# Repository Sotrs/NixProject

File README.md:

# NixProject By Sotiris Zannetos Readme Work In Progress
Nixe Clock Project Including Electronics, Software and 3d Designing for Enclosure

By looking at the Nixie Datasheet we know that each tube requires 10 different Inputs to turn each digit on (Will not be using the commas). For this clock I will be using the classic IN-14 Tube.

My MCU of choice is the ATmega328P which is a very popular choice that is also used in Arduino devices, it has a very well established documentation and support and can also be programmed using the Arduino IDE. This is exactly what I need as the Arduino IDE by itself is simple and easy to use and is also very well documented and supported by its community.

Now in order to turn on the tubes we need a driver that can take the digital output of the ATmega and turn on the particular digit we want to light up. We have a few problems we must solve in order to achieve that:
1. The clock we want to create will be a Six-Digit clock "HH:MM:SS" meaning we need 60 individual outputs. Unfortunately the Atmega328P can maxes out at '18', including the analog outputs as digital I/O's.
2. The tubes require a whopping 170V DC in order to light up and about 145V DC to keep running. That is not something we can control using only the digital outputs of a 5V DC Microcontroller.

To solve the first problem we can simply use dedicated Drivers, in fact a BCD-TO-DECIMAL Decoder was made specifically for driving Nixie Tubes known as the **SN74141** or its Soviet Sibling the **K155ID1**. This automatically solves the second problem as well as these drivers were created to handle the high voltage. The use of such drivers makes our project very simple as we can use 1 driver for each tube which brings us down from 60 individual outputs to 24 with each driver requiring 4 bits of info to control the 10 digits.

However, the problem is yet to be solved as 24 outputs are still more than what our MCU can give, we can tackle this problem using an I/O Expander with a Serial Interface. Utilizing THE I^2C Interface of the ATmega we can use I/O Expanders such as the **MCP23017** that will give us 16 extra I/O which are now more than enough of what we need. With that we can sucessfuly drive our nixie tubes using the MCU's Outputs!

We are still missing two critical components in our clock, while the ATmega328P can use its Internal 8MHz crystal Oscillator or an external 16MHz one they are still not very good at time keeping as this is not their intended use, also it will be unable to keep time while it is not powered. This is why we will use an RTC which is a device made for timekeeping. My choice of RTC is the **DS3231** with a simple I2C connection and a cr2032 battery it can keep time with an insane 2PPM accuracy.

Last but definetely not least we will need a DC-DC boost converter, the clock will be powered by 5V DC so we will need to take that 5V and convert it to 170V DC for our tubes. An easy solution to this is to use a premade module made by OMNIXIE called the **NCH8200HV**. It is small, efficient and widely used by many nixie clock creators, it simply does its job. It is the only premade module used in this project, dont't worry it will be embedded in our PCB very neatly and discreetly along with the other components.

Now, we have all of our components:
1. MCU -> ATmega 328p-AU
2. Tubes -> IN-14 Gazotron
3. RTC -> DS3231
4. I/O Expander -> MCP 23017  
5. DC-DC Converter -> NCH8200HV
6. SN74141 Drivers -> SN74141/K155ID1

We are ready to start the Electronic architecture, I will be using KiCad to create the schematics and PCB design, an open source and intuitive Electronic design software. Two push buttons will be used to control and set the time by the user. Also in order to program the arduino using the type C interface we will need an external USB to Serial device or in this case we will integrade an FTDI chip directily into our board using the very popular FT232RL.

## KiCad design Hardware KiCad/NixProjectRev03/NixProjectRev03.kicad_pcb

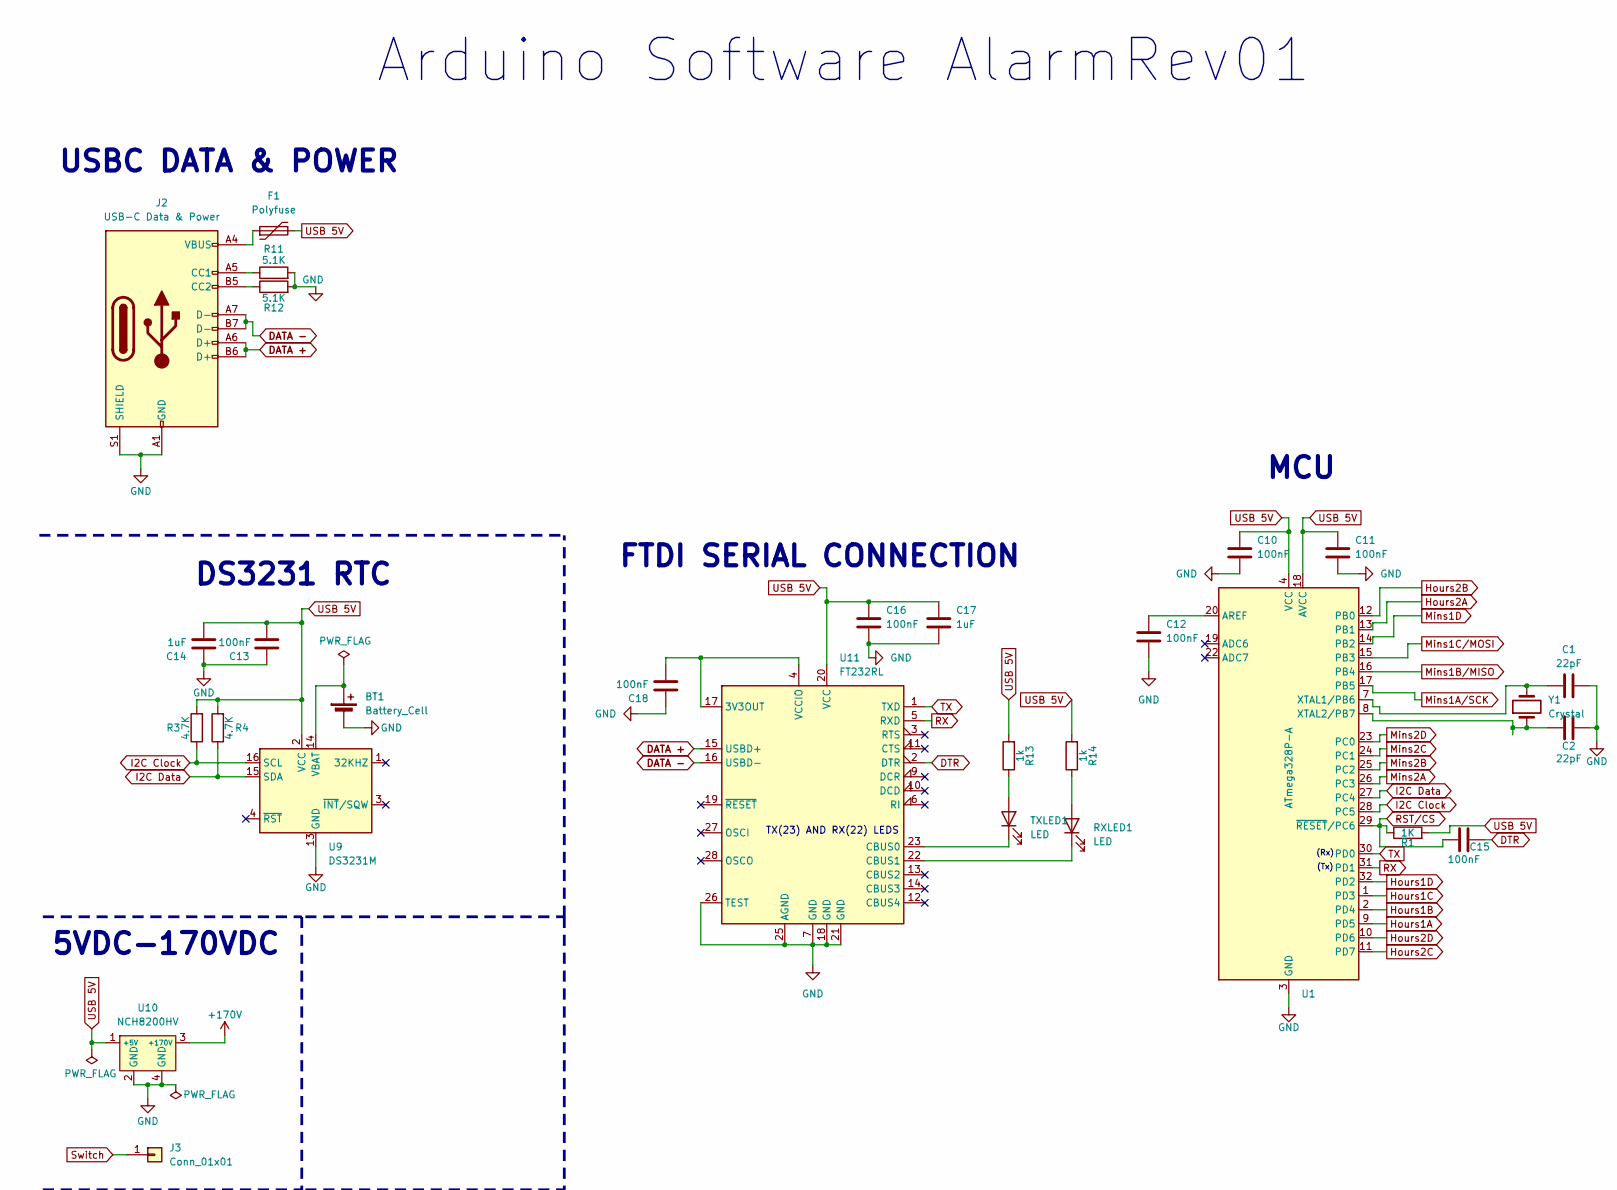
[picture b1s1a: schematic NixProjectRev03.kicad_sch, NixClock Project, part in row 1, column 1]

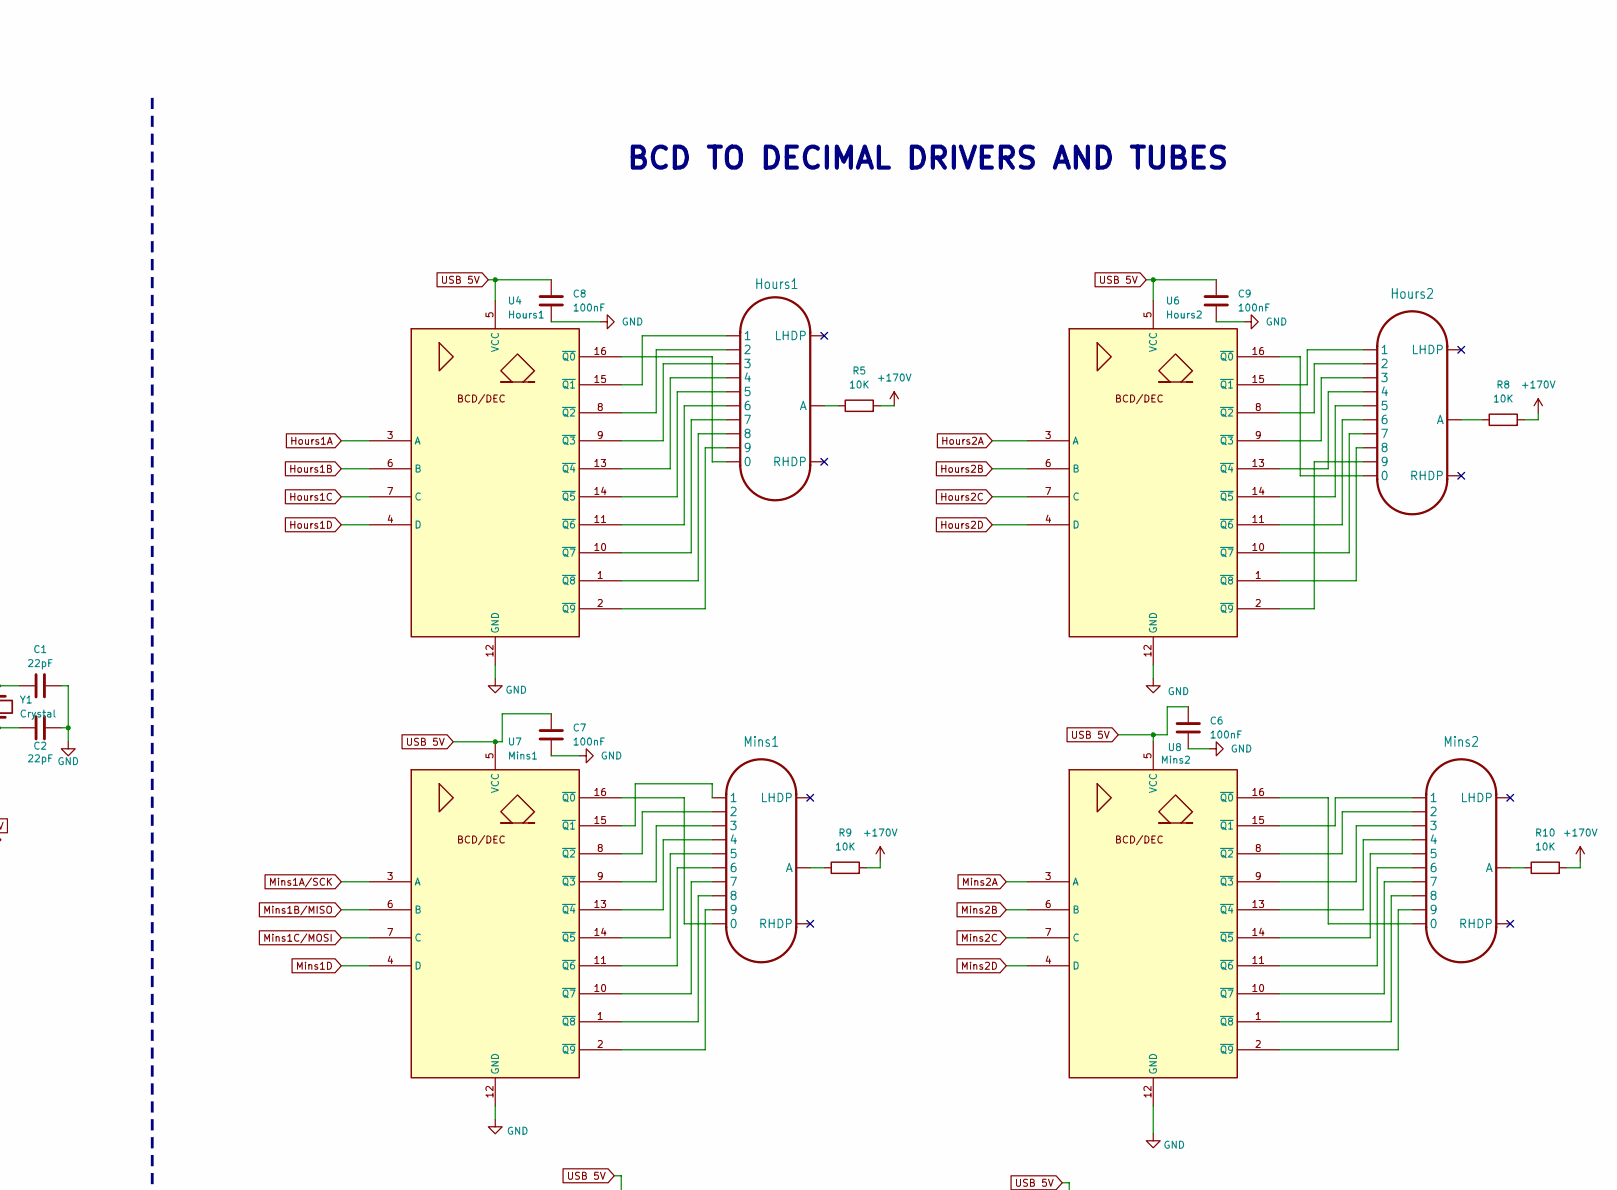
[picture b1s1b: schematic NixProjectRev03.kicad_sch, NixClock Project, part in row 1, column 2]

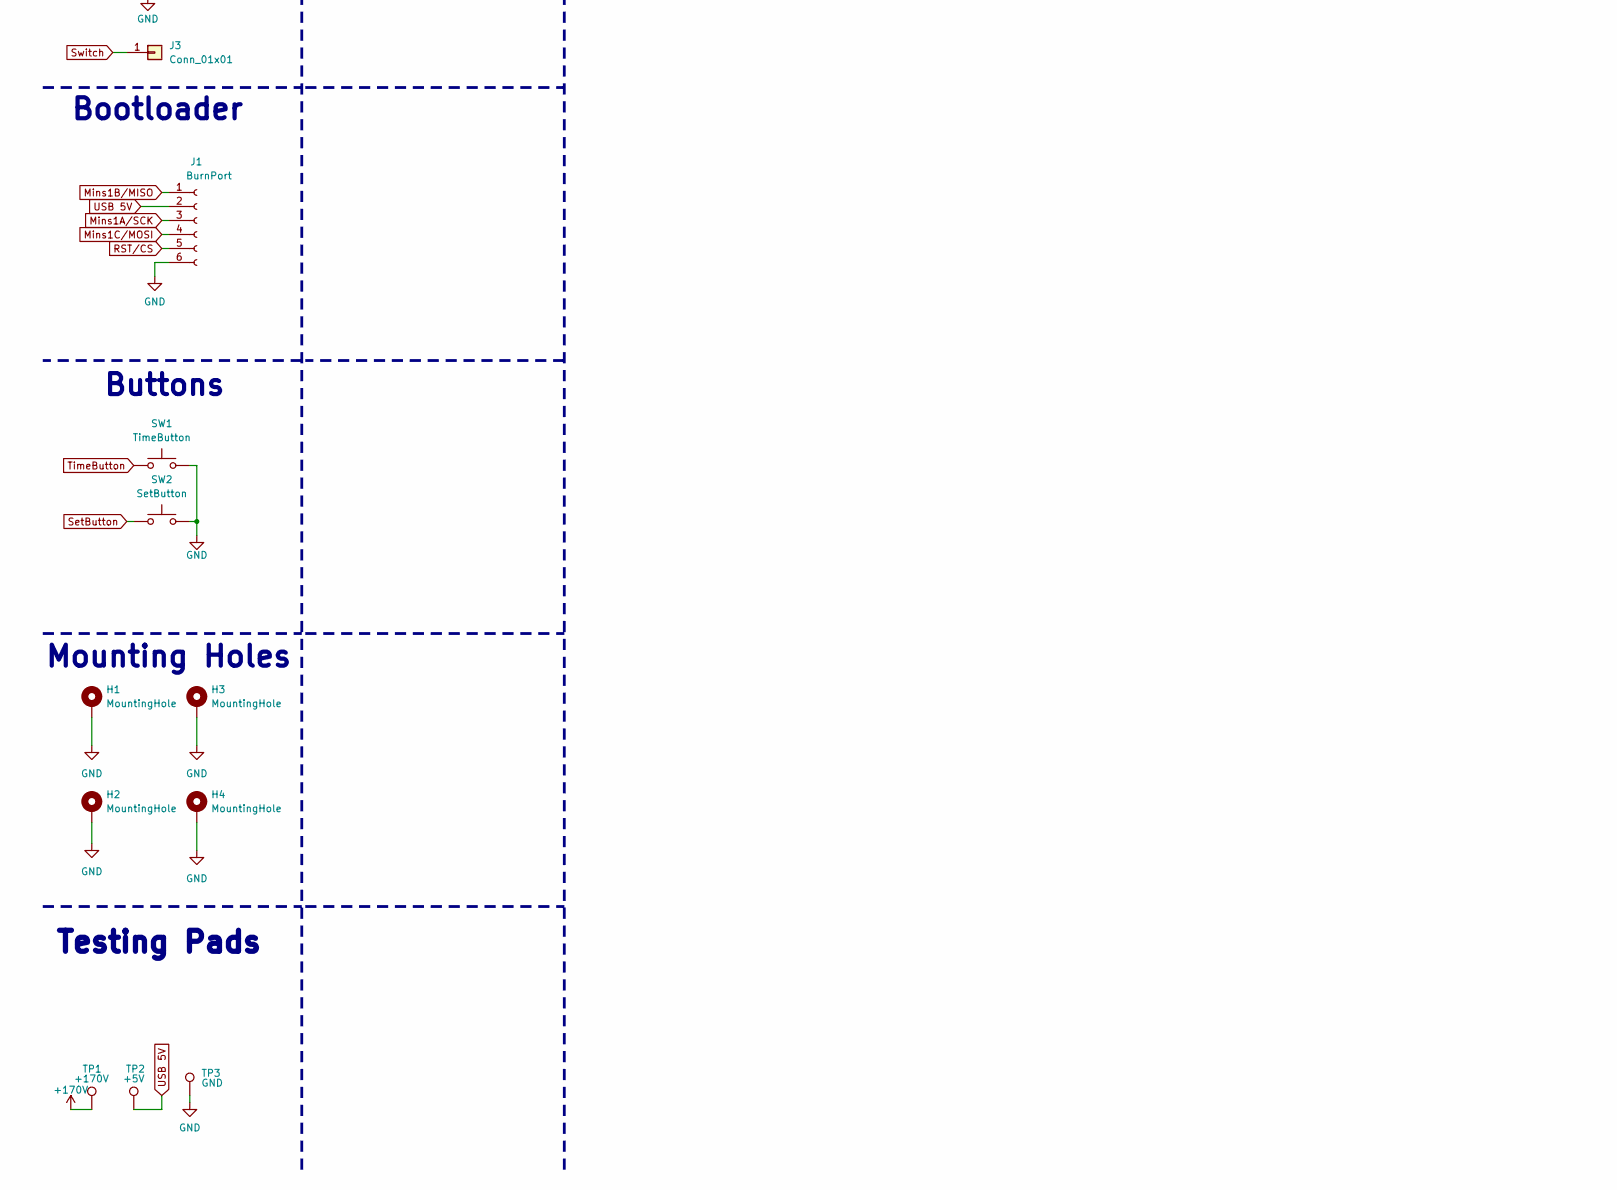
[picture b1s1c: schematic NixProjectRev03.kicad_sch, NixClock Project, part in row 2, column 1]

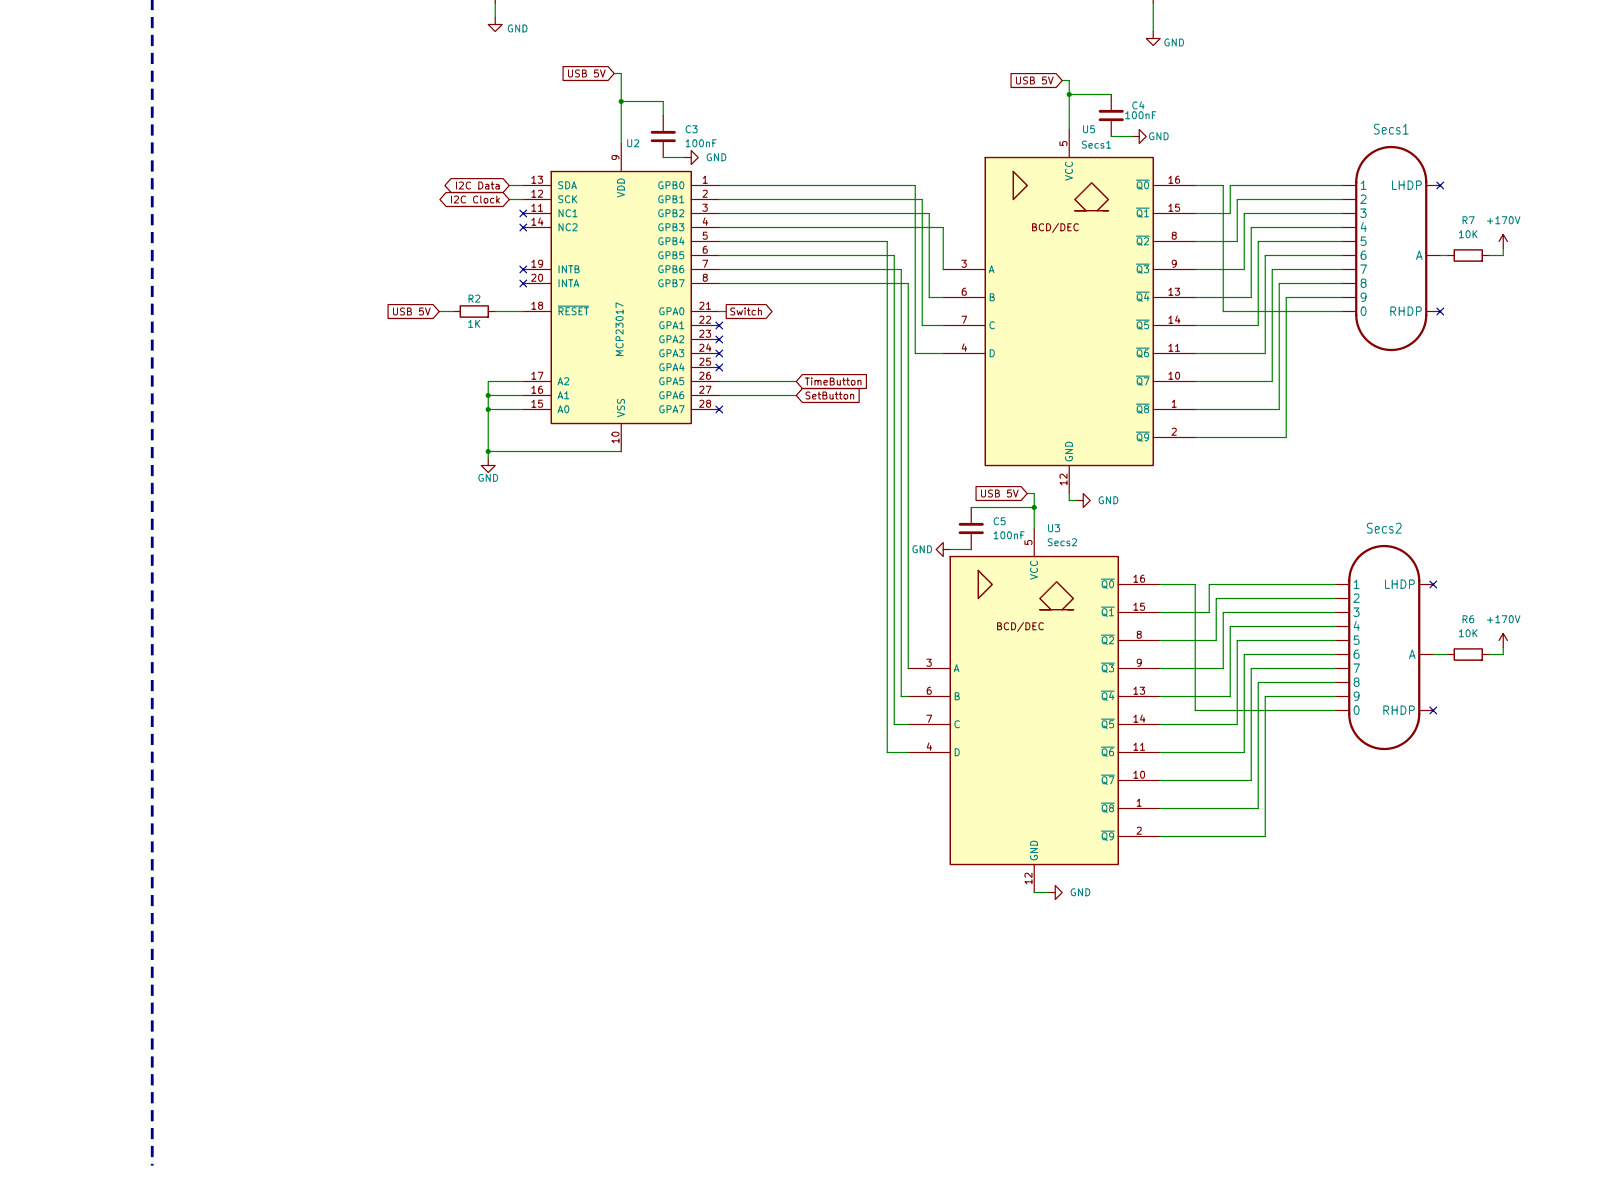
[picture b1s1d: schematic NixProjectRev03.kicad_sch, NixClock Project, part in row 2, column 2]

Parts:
BT1: Battery_Cell; Battery Holder SMD CR2032
C1, C2: 22pF; C_1206_3216Metric_Pad1.33x1.80mm_HandSolder
C3, C4, C5, C6, C7, C8, C9, C10, C11, C12, C13, C15, C16, C18: 100nF; C_1206_3216Metric_Pad1.33x1.80mm_HandSolder
C14, C17: 1uF; C_1206_3216Metric_Pad1.33x1.80mm_HandSolder
F1: Polyfuse; Fuse_1206_3216Metric
H1, H2, H3, H4: MountingHole; MountingHole_4.3mm_M4_DIN965_Pad
Hours1, Hours2: nixies-us-IN-14
J1: BurnPort; PinHeader_2x03_P2.54mm_Vertical
J2: USB-C Data & Power; USB_C_Receptacle_GCT_USB4105-xx-A_16P_TopMnt_Horizontal
J3: Conn_01x01; SolderWire-0.1sqmm_1x01_D0.4mm_OD1mm
Mins1, Mins2: nixies-us-IN-14
R1, R2: 1K; R_0805_2012Metric_Pad1.20x1.40mm_HandSolder
R3, R4: 4.7K; R_0805_2012Metric_Pad1.20x1.40mm_HandSolder
R5, R6, R7, R8, R9, R10: 10K; R_Axial_DIN0204_L3.6mm_D1.6mm_P7.62mm_Horizontal
R11, R12: 5.1K; R_0805_2012Metric_Pad1.20x1.40mm_HandSolder
R13, R14: 1k; R_1206_3216Metric_Pad1.30x1.75mm_HandSolder
RXLED1: LED; LED_1206_3216Metric_Pad1.42x1.75mm_HandSolder
SW1: TimeButton; SW_PUSH-12mm
SW2: SetButton; SW_PUSH-12mm
Secs1, Secs2: nixies-us-IN-14
TP1: +170V; TestPoint_Pad_D2.0mm
TP2: +5V; TestPoint_Pad_D2.0mm
TP3: GND; TestPoint_Pad_D2.0mm
TXLED1: LED; LED_1206_3216Metric_Pad1.42x1.75mm_HandSolder
U1: ATmega328P-A; TQFP-32_7x7mm_P0.8mm
U2: MCP23017; SOIC-28W_7.5x18.7mm_P1.27mm
U3: Secs2; DIP-16_W7.62mm
U4: Hours1; DIP-16_W7.62mm
U5: Secs1; DIP-16_W7.62mm
U6: Hours2; DIP-16_W7.62mm
U7: Mins1; DIP-16_W7.62mm
U8: Mins2; DIP-16_W7.62mm
U9: DS3231M; SOIC-16W_7.5x10.3mm_P1.27mm
U10: NCH8200HV
U11: FT232RL; SSOP-28_5.3x10.2mm_P0.65mm
Y1: Crystal; Crystal_SMD

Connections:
+170V: R5.2, R6.2, R7.2, R8.2, R9.2, R10.2, TP1.1, U10.3 (+170V)
DATA +: J2.A6 (D+), J2.B6 (D+), U11.15 (USBD+)
DATA -: J2.A7 (D-), J2.B7 (D-), U11.16 (USBD-)
DTR: C15.2, U11.2 (DTR)
GND: BT1.2 (-), C1.2, C2.2, C3.1, C4.1, C5.2, C6.2, C7.2, C8.2, C9.2, C10.2, C11.2, C12.2, C13.1, C14.1, C16.2, C17.2, C18.1, H1.1, H2.1, H3.1, H4.1, J1.6, J2.A1 (GND), J2.A12 (GND), J2.B1 (GND), J2.B12 (GND), J2.S1 (SHIELD), R11.2, R12.2, SW1.2, SW2.2, TP3.1, U1.3 (GND), U1.5 (GND), U1.21 (GND), U2.10 (VSS), U2.15 (A0), U2.16 (A1), U2.17 (A2), U3.12 (GND), U4.12 (GND), U5.12 (GND), U6.12 (GND), U7.12 (GND), U8.12 (GND), U9.5 (GND), U9.6 (GND), U9.7 (GND), U9.8 (GND), U9.9 (GND), U9.10 (GND), U9.11 (GND), U9.12 (GND), U9.13 (GND), U10.2 (GND), U10.4 (GND), U11.7 (GND), U11.18 (GND), U11.21 (GND), U11.25 (AGND), U11.26 (TEST)
Hours1A: U1.9 (PD5), U4.3 (A)
Hours1B: U1.2 (PD4), U4.6 (B)
Hours1C: U1.1 (PD3), U4.7 (C)
Hours1D: U1.32 (PD2), U4.4 (D)
Hours2A: U1.13 (PB1), U6.3 (A)
Hours2B: U1.12 (PB0), U6.6 (B)
Hours2C: U1.11 (PD7), U6.7 (C)
Hours2D: U1.10 (PD6), U6.4 (D)
I2C Clock: R3.1, U1.28 (PC5), U2.12 (SCK), U9.16 (SCL)
I2C Data: R4.1, U1.27 (PC4), U2.13 (SDA), U9.15 (SDA)
Mins1A/SCK: J1.3, U1.17 (PB5), U7.3 (A)
Mins1B/MISO: J1.1, U1.16 (PB4), U7.6 (B)
Mins1C/MOSI: J1.4, U1.15 (PB3), U7.7 (C)
Mins1D: U1.14 (PB2), U7.4 (D)
Mins2A: U1.26 (PC3), U8.3 (A)
Mins2B: U1.25 (PC2), U8.6 (B)
Mins2C: U1.24 (PC1), U8.7 (C)
Mins2D: U1.23 (PC0), U8.4 (D)
unnamed: BT1.1 (+), U9.14 (VBAT)
unnamed: F1.1, J2.A4 (VBUS), J2.A9 (VBUS), J2.B4 (VBUS), J2.B9 (VBUS)
unnamed: Hours1.A, R5.1
unnamed: Hours2.A, R8.1
unnamed: J2.A5 (CC1), R11.1
unnamed: J2.B5 (CC2), R12.1
unnamed: Mins1.A, R9.1
unnamed: Mins2.A, R10.1
unnamed: R6.1, Secs2.A
unnamed: R7.1, Secs1.A
unnamed: R14.1, RXLED1.2 (A)
unnamed: RXLED1.1 (K), U11.22 (CBUS1)
unnamed: R13.1, TXLED1.2 (A)
unnamed: TXLED1.1 (K), U11.23 (CBUS0)
unnamed: C12.1, U1.20 (AREF)
unnamed: C1.1, U1.7 (XTAL1/PB6), Y1.2
unnamed: C2.1, U1.8 (XTAL2/PB7), Y1.1
unnamed: U2.1 (GPB0), U5.4 (D)
unnamed: U2.2 (GPB1), U5.7 (C)
unnamed: U2.3 (GPB2), U5.6 (B)
unnamed: U2.4 (GPB3), U5.3 (A)
unnamed: U2.5 (GPB4), U3.4 (D)
unnamed: U2.6 (GPB5), U3.7 (C)
unnamed: U2.7 (GPB6), U3.6 (B)
unnamed: U2.8 (GPB7), U3.3 (A)
unnamed: R2.2, U2.18 (~RESET)
unnamed: Secs2.0, U3.16 (~Q0)
unnamed: Secs2.1, U3.15 (~Q1)
unnamed: Secs2.2, U3.8 (~Q2)
unnamed: Secs2.3, U3.9 (~Q3)
unnamed: Secs2.4, U3.13 (~Q4)
unnamed: Secs2.5, U3.14 (~Q5)
unnamed: Secs2.6, U3.11 (~Q6)
unnamed: Secs2.7, U3.10 (~Q7)
unnamed: Secs2.8, U3.1 (~Q8)
unnamed: Secs2.9, U3.2 (~Q9)
unnamed: Hours1.0, U4.16 (~Q0)
unnamed: Hours1.1, U4.15 (~Q1)
unnamed: Hours1.2, U4.8 (~Q2)
unnamed: Hours1.3, U4.9 (~Q3)
unnamed: Hours1.4, U4.13 (~Q4)
unnamed: Hours1.5, U4.14 (~Q5)
unnamed: Hours1.6, U4.11 (~Q6)
unnamed: Hours1.7, U4.10 (~Q7)
unnamed: Hours1.8, U4.1 (~Q8)
unnamed: Hours1.9, U4.2 (~Q9)
unnamed: Secs1.0, U5.16 (~Q0)
unnamed: Secs1.1, U5.15 (~Q1)
unnamed: Secs1.2, U5.8 (~Q2)
unnamed: Secs1.3, U5.9 (~Q3)
unnamed: Secs1.4, U5.13 (~Q4)
unnamed: Secs1.5, U5.14 (~Q5)
unnamed: Secs1.6, U5.11 (~Q6)
unnamed: Secs1.7, U5.10 (~Q7)
unnamed: Secs1.8, U5.1 (~Q8)
unnamed: Secs1.9, U5.2 (~Q9)
unnamed: Hours2.0, U6.16 (~Q0)
unnamed: Hours2.1, U6.15 (~Q1)
unnamed: Hours2.2, U6.8 (~Q2)
unnamed: Hours2.3, U6.9 (~Q3)
unnamed: Hours2.4, U6.13 (~Q4)
unnamed: Hours2.5, U6.14 (~Q5)
unnamed: Hours2.6, U6.11 (~Q6)
unnamed: Hours2.7, U6.10 (~Q7)
unnamed: Hours2.8, U6.1 (~Q8)
unnamed: Hours2.9, U6.2 (~Q9)
unnamed: Mins1.0, U7.16 (~Q0)
unnamed: Mins1.1, U7.15 (~Q1)
unnamed: Mins1.2, U7.8 (~Q2)
unnamed: Mins1.3, U7.9 (~Q3)
unnamed: Mins1.4, U7.13 (~Q4)
unnamed: Mins1.5, U7.14 (~Q5)
unnamed: Mins1.6, U7.11 (~Q6)
unnamed: Mins1.7, U7.10 (~Q7)
unnamed: Mins1.8, U7.1 (~Q8)
unnamed: Mins1.9, U7.2 (~Q9)
unnamed: Mins2.0, U8.16 (~Q0)
unnamed: Mins2.1, U8.15 (~Q1)
unnamed: Mins2.2, U8.8 (~Q2)
unnamed: Mins2.3, U8.9 (~Q3)
unnamed: Mins2.4, U8.13 (~Q4)
unnamed: Mins2.5, U8.14 (~Q5)
unnamed: Mins2.6, U8.11 (~Q6)
unnamed: Mins2.7, U8.10 (~Q7)
unnamed: Mins2.8, U8.1 (~Q8)
unnamed: Mins2.9, U8.2 (~Q9)
unnamed: C18.2, U11.4 (VCCIO), U11.17 (3V3OUT)
RST/CS: C15.1, J1.5, R1.1, U1.29 (~RESET/PC6)
RX: U1.31 (PD1), U11.5 (RXD)
SetButton: SW2.1, U2.27 (GPA6)
Switch: J3.1, U2.21 (GPA0)
TX: U1.30 (PD0), U11.1 (TXD)
TimeButton: SW1.1, U2.26 (GPA5)
USB 5V: C3.2, C4.2, C5.1, C6.1, C7.1, C8.1, C9.1, C10.1, C11.1, C13.2, C14.2, C16.1, C17.1, F1.2, J1.2, R1.2, R2.1, R3.2, R4.2, R13.2, R14.2, TP2.1, U1.4 (VCC), U1.6 (VCC), U1.18 (AVCC), U2.9 (VDD), U3.5 (VCC), U4.5 (VCC), U5.5 (VCC), U6.5 (VCC), U7.5 (VCC), U8.5 (VCC), U9.2 (VCC), U10.1 (+5V), U11.20 (VCC)

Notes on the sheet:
DS3231 RTC
FTDI SERIAL CONNECTION
(Rx)
5VDC-170VDC
USBC DATA & POWER
(Tx)
Arduino Software AlarmRev01
BCD TO DECIMAL DRIVERS AND TUBES
TX(23) AND RX(22) LEDS
Buttons
Testing Pads
Bootloader
MCU
Mounting Holes

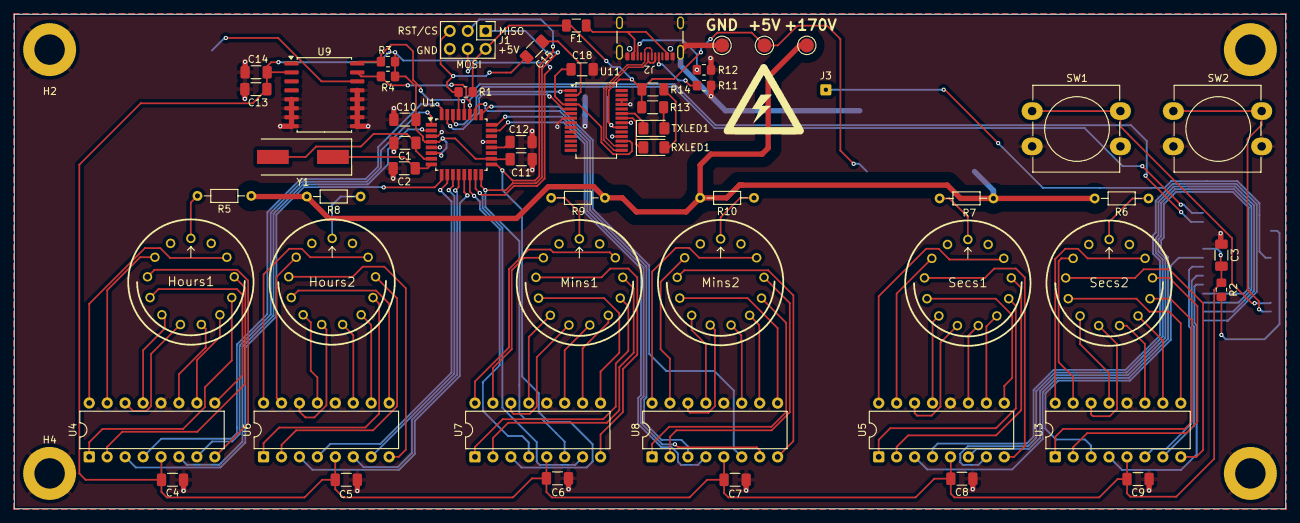
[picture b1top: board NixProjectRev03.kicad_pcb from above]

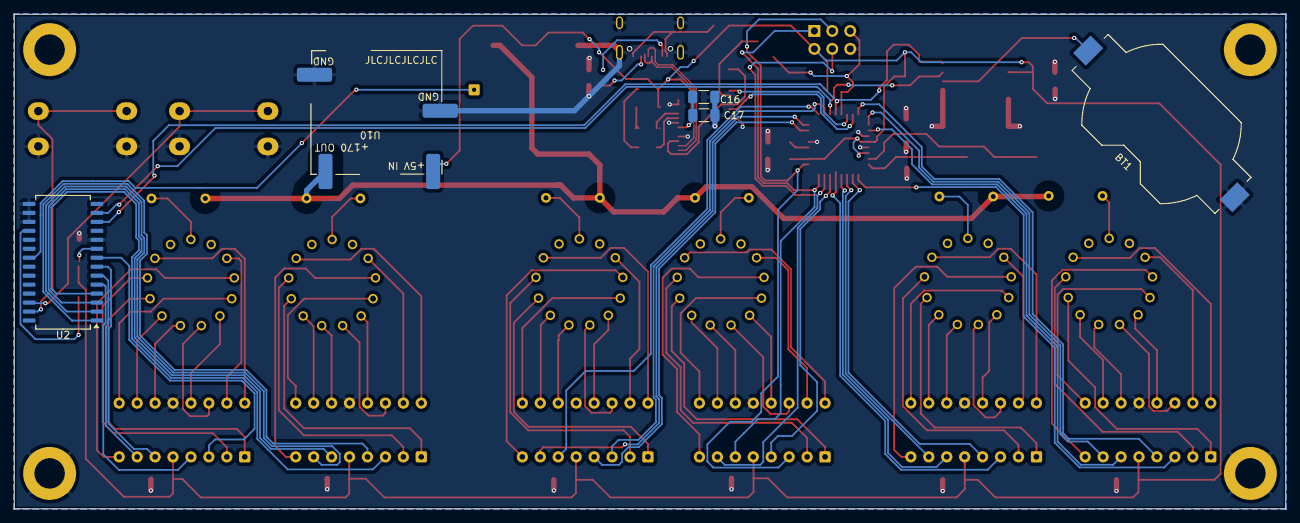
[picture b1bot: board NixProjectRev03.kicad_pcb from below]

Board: 2 copper layers, 180.0 x 70.0 mm, 66 parts (5 on the bottom side), 117 nets.

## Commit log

2025-05-25 Add files via upload
    The First stable Revision of the clock's software
2025-05-25 Create Adafruit_MCP23017_Arduino_Library
2025-05-25 Add files via upload
    Main Software for Nixie Clock
2025-05-25 Renamed Hardware Folder
2025-05-25 Rename Kicad Folder
2025-05-25 Create LICENSE
2025-05-25 Add Arduino libs

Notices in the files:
Hardware KiCad/NixProjectRev03/NixProjectRev03.kicad_pcb:
creativecommons.org/licenses/by/4.0
License: CC BY  4.0
